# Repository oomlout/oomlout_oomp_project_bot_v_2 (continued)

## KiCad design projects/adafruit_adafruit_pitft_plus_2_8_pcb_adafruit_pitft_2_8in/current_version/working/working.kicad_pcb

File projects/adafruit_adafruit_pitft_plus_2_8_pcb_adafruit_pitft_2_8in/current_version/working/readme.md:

# adafruit_pitft_plus_2_8_pcb
 
## summary 
* id: adafruit_adafruit_pitft_plus_2_8_pcb_adafruit_pitft_2_8in
* user: adafruit
* name: adafruit_pitft_plus_2_8_pcb
* board: adafruit_pitft_2_8in
* repo: https://github.com/adafruit/Adafruit-PiTFT-Plus-2.8-PCB

* src_file_repo_sch: 
* src_file_repo_sch_link: https://github.com/adafruit/Adafruit-PiTFT-Plus-2.8-PCB/tree/master/
* full details link: https://github.com/oomlout/oomlout_oomp_project_bot_v_2/tree/main/projects/adafruit_adafruit_pitft_plus_2_8_pcb_adafruit_pitft_2_8in/current_version/working  

## schematic  
  
[schematic (pdf)](working_schematic.pdf) 

## pcb  

[board (pdf)](working.pdf)  

## working_bom
| Id | Designator | Footprint | Quantity | Designation | Supplier and ref |  | None | 
| --- | --- | --- | --- | --- | --- | --- | --- | 
| 1 | U$15,U$3,U$17,U$40,U$16 | MOUNTINGHOLE_3.0_PLATEDTHIN | 5 | MOUNTINGHOLE3.0THIN |  |  | [''] | 
| 2 | R1,R2,R4,R3 | 0805-NO | 4 | 100 |  |  | [''] | 
| 3 | R13,R12,R14,R9 | 0805-NO | 4 | 3.9K |  |  | [''] | 
| 4 | R18,R16,R15,R17 | 0805-NO | 4 | 0 |  |  | [''] | 
| 5 | D1,D2 | SOD-323 | 2 | 1N4148 |  |  | [''] | 
| 6 | R6,R7 | 0805-NO | 2 | 10K |  |  | [''] | 
| 7 | IC5 | SOT23 | 1 | APX803 |  |  | [''] | 
| 8 | U$12 | PCBFEAT-REV-040 | 1 |  |  |  | [''] | 
| 9 | U$18,U$10,U$11 | FIDUCIAL_1MM | 3 | FIDUCIAL" |  |  | [''] | 
| 10 | R11,R10 | 0805-NO | 2 | 22 |  |  | [''] | 
| 11 | JP3 | 2X20_SMT_MALE | 1 |  |  |  | [''] | 
| 12 | U2 | QFN16_3MM | 1 | STMPE811 |  |  | [''] | 
| 13 | WPJ1,WPJ0 | SOLDERJUMPER_CLOSEDWIRE | 2 |  |  |  | [''] | 
| 14 | C3,C4,C2 | 0805-NO | 3 | 0.1uF |  |  | [''] | 
| 15 | U1 | SOIC8_150MIL | 1 | CAT24C32 |  |  | [''] | 
| 16 | R8 | 0805-NO | 1 | DNP |  |  | [''] | 
| 17 | U$42 | ADAFRUIT_TEXT_30MM | 1 |  |  |  | [''] | 
| 18 | C1,C5 | 0805-NO | 2 | 10uF |  |  | [''] | 
| 19 | Q2 | SOT23-WIDE | 1 | BSS138 |  |  | [''] | 
| 20 | SW2,SW4,SW3,SW1 | TACT_PANA-EVQ | 4 |  |  |  | [''] | 
| 21 | U$23 | ADAFRUIT_TEXT_20MM | 1 |  |  |  | [''] | 
| 22 | U$2 | TFT_2.83IN_240X320_50PIN | 1 | DISP_LCD_240X320_50PIN_2.8IN |  |  | [''] | 
| 23 | RPI1 | RASPBERRYPI_BPLUS_SHIELD_NODIM | 1 | RASPBERRYPI_BPLUS_SHIELD_NODIM |  |  | [''] | 

## bom_schematic
| Ref | Qnty | Value | Cmp name | Footprint | Description | Vendor | DNP | 
| --- | --- | --- | --- | --- | --- | --- | --- | 
| C1, C5 | 2 | 10uF | CAP_CERAMIC0805-NOOUTLINE | working:0805-NO |  |  |  | 
| C2, C3, C4 | 3 | 0.1uF | CAP_CERAMIC0805-NOOUTLINE | working:0805-NO |  |  |  | 
| D1, D2 | 2 | 1N4148 | DIODESOD-323 | working:SOD-323 |  |  |  | 
| IC5 | 1 | APX803 | AXP083-SAG | working:SOT23 |  |  |  | 
| JP3 | 1 | PINHD-2X20_SMT | PINHD-2X20_SMT | working:2X20_SMT_MALE |  |  |  | 
| Q2 | 1 | BSS138 | MOSFET-NWIDE | working:SOT23-WIDE |  |  |  | 
| R1, R2, R3, R4 | 4 | 100 | RESISTOR0805_NOOUTLINE | working:0805-NO |  |  |  | 
| R6, R7 | 2 | 10K | RESISTOR0805_NOOUTLINE | working:0805-NO |  |  |  | 
| R8 | 1 | DNP | RESISTOR0805_NOOUTLINE | working:0805-NO |  |  |  | 
| R9, R12, R13, R14 | 4 | 3.9K | RESISTOR0805_NOOUTLINE | working:0805-NO |  |  |  | 
| R10, R11 | 2 | 22 | RESISTOR0805_NOOUTLINE | working:0805-NO |  |  |  | 
| R15, R16, R17, R18 | 4 | 0 | RESISTOR0805_NOOUTLINE | working:0805-NO |  |  |  | 
| RPI1 | 1 | RASPBERRYPI_BPLUS_SHIELD_NODIM | RASPBERRYPI_BPLUS_SHIELD_NODIM | working:RASPBERRYPI_BPLUS_SHIELD_NODIM |  |  |  | 
| SW1, SW2, SW3, SW4 | 4 | SWITCH_PUSHBUTTONEVQ-PE | SWITCH_PUSHBUTTONEVQ-PE | working:TACT_PANA-EVQ |  |  |  | 
| U1 | 1 | CAT24C32 | EEPROM_I2C_SOIC8_GENERIC | working:SOIC8_150MIL |  |  |  | 
| U2 | 1 | STMPE811 | STMPE610 | working:QFN16_3MM |  |  |  | 
| U$2 | 1 | DISP_LCD_240X320_50PIN_2.8IN | DISP_LCD_240X320_50PIN_2.8IN | working:TFT_2.83IN_240X320_50PIN |  |  |  | 
| U$3, U$15, U$16, U$17, U$40 | 5 | MOUNTINGHOLE3.0THIN | MOUNTINGHOLE3.0THIN | working:MOUNTINGHOLE_3.0_PLATEDTHIN |  |  |  | 
| U$10, U$11, U$18 | 3 | FIDUCIAL"" | FIDUCIAL{dblquote}{dblquote} | working:FIDUCIAL_1MM |  |  |  | 
| WPJ0, WPJ1 | 2 | SOLDERJUMPERCLOSED | SOLDERJUMPERCLOSED | working:SOLDERJUMPER_CLOSEDWIRE |  |  |  | 

## mounting_holes
| x | y | package | value | ref | size | 
| --- | --- | --- | --- | --- | --- | 
| 0.03 | 77.9 | MOUNTINGHOLE_3.0_PLATEDTHIN | MOUNTINGHOLE3.0THIN | U$3 | m3 | 
| 49.02 | 77.9 | MOUNTINGHOLE_3.0_PLATEDTHIN | MOUNTINGHOLE3.0THIN | U$15 | m3 | 
| 49.0 | 0.0 | MOUNTINGHOLE_3.0_PLATEDTHIN | MOUNTINGHOLE3.0THIN | U$16 | m3 | 
| 0.0 | 0.0 | MOUNTINGHOLE_3.0_PLATEDTHIN | MOUNTINGHOLE3.0THIN | U$17 | m3 | 
| 0.03 | 19.91 | MOUNTINGHOLE_3.0_PLATEDTHIN | MOUNTINGHOLE3.0THIN | U$40 | m3 |

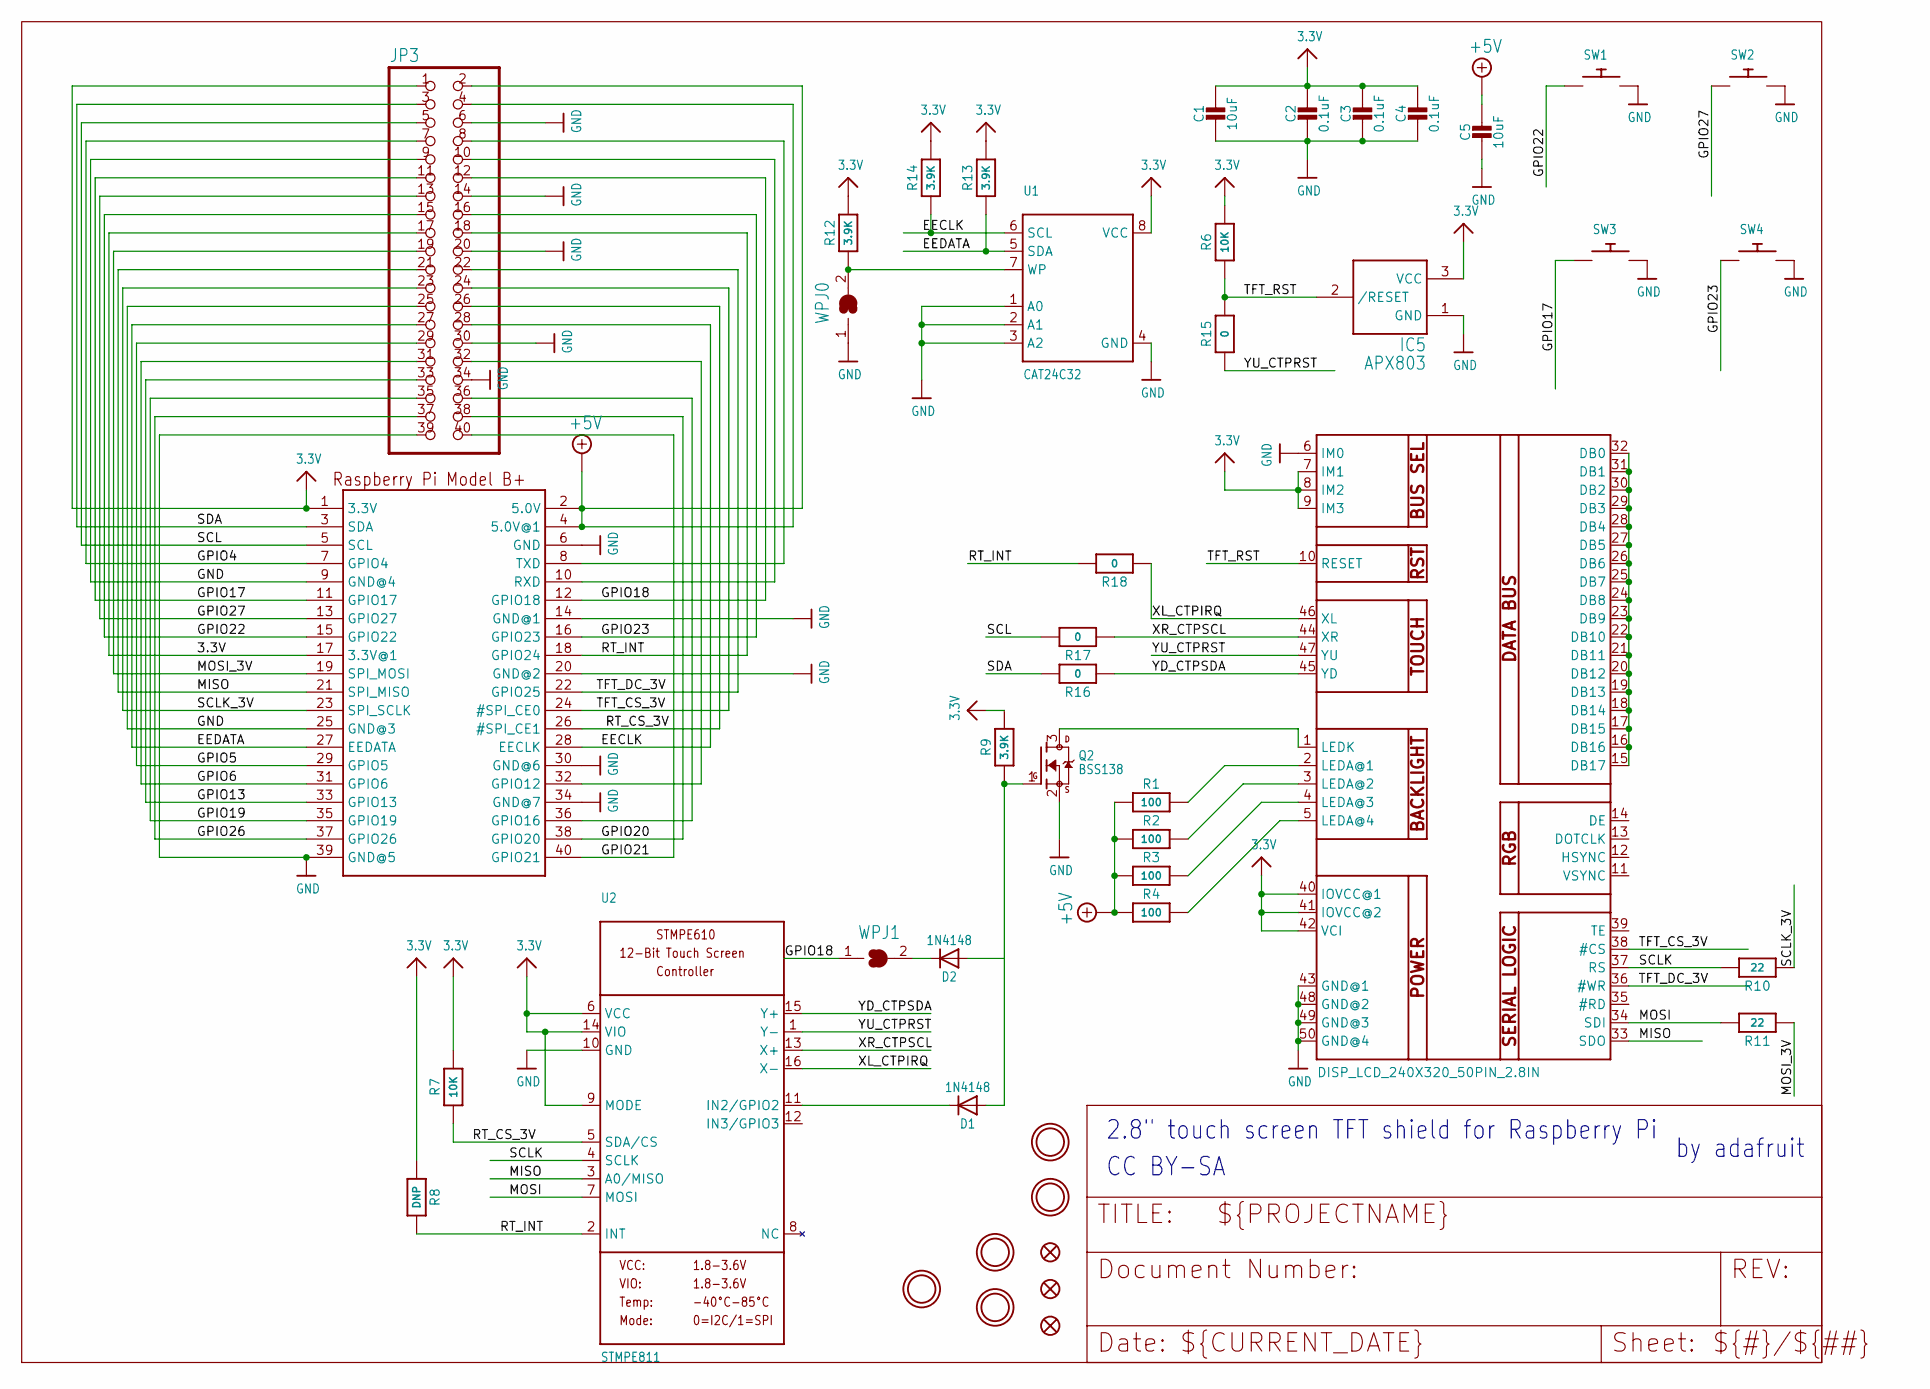
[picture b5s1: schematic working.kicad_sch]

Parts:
C1, C5: 10uF; 0805-NO
C2, C3, C4: 0.1uF; 0805-NO
D1, D2: 1N4148; SOD-323
IC5: APX803; SOT23
JP3: PINHD-2X20_SMT; 2X20_SMT_MALE
Q2: BSS138; SOT23-WIDE
R1, R2, R3, R4: 100; 0805-NO
R6, R7: 10K; 0805-NO
R8: DNP; 0805-NO
R9, R12, R13, R14: 3.9K; 0805-NO
R10, R11: 22; 0805-NO
R15, R16, R17, R18: 0; 0805-NO
RPI1: RASPBERRYPI_BPLUS_SHIELD_NODIM
SW1, SW2, SW3, SW4: SWITCH_PUSHBUTTONEVQ-PE; TACT_PANA-EVQ
U1: CAT24C32; SOIC8_150MIL
U2: STMPE811; QFN16_3MM
U$2: DISP_LCD_240X320_50PIN_2.8IN; TFT_2.83IN_240X320_50PIN
U$3, U$15, U$16, U$17, U$40: MOUNTINGHOLE3.0THIN; MOUNTINGHOLE_3.0_PLATEDTHIN
U$10, U$11, U$18: FIDUCIAL""; FIDUCIAL_1MM
WPJ0, WPJ1: SOLDERJUMPERCLOSED; SOLDERJUMPER_CLOSEDWIRE

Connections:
3.3V: C1.1, C2.1, C3.1, C4.1, IC5.3 (VCC), JP3.1, JP3.17, R6.2, R7.2, R8.1, R9.2, R12.2, R13.2, R14.2, RPI1.1 (3.3V), RPI1.17 (3.3V@1), U1.8 (VCC), U2.6 (VCC), U2.9 (MODE), U2.14 (VIO), U$2.7 (IM1), U$2.8 (IM2), U$2.9 (IM3), U$2.40 (IOVCC@1), U$2.41 (IOVCC@2), U$2.42 (VCI)
+5V: C5.1, JP3.2, JP3.4, R1.1, R2.1, R3.1, R4.1, RPI1.2 (5.0V), RPI1.4 (5.0V@1)
EECLK: JP3.28, R14.1, RPI1.28 (EECLK), U1.6 (SCL)
EEDATA: JP3.27, R13.1, RPI1.27 (EEDATA), U1.5 (SDA)
GND: C1.2, C2.2, C3.2, C4.2, C5.2, IC5.1 (GND), JP3.6, JP3.9, JP3.14, JP3.20, JP3.25, JP3.30, JP3.34, JP3.39, Q2.2 (S), RPI1.6 (GND), RPI1.9 (GND@4), RPI1.14 (GND@1), RPI1.20 (GND@2), RPI1.25 (GND@3), RPI1.30 (GND@6), RPI1.34 (GND@7), RPI1.39 (GND@5), SW1.P$2, SW2.P$2, SW3.P$2, SW4.P$2, U1.1 (A0), U1.2 (A1), U1.3 (A2), U1.4 (GND), U2.10 (GND), U$2.6 (IM0), U$2.43 (GND@1), U$2.48 (GND@2), U$2.49 (GND@3), U$2.50 (GND@4), WPJ0.1
GPIO4: JP3.7, RPI1.7 (GPIO4)
GPIO5: JP3.29, RPI1.29 (GPIO5)
GPIO6: JP3.31, RPI1.31 (GPIO6)
GPIO12: JP3.32, RPI1.32 (GPIO12)
GPIO13: JP3.33, RPI1.33 (GPIO13)
GPIO16: JP3.36, RPI1.36 (GPIO16)
GPIO17: JP3.11, RPI1.11 (GPIO17), SW3.P$1
GPIO18: JP3.12, RPI1.12 (GPIO18), WPJ1.1
GPIO19: JP3.35, RPI1.35 (GPIO19)
GPIO20: JP3.38, RPI1.38 (GPIO20)
GPIO21: JP3.40, RPI1.40 (GPIO21)
GPIO22: JP3.15, RPI1.15 (GPIO22), SW1.P$1
GPIO23: JP3.16, RPI1.16 (GPIO23), SW4.P$1
GPIO26: JP3.37, RPI1.37 (GPIO26)
GPIO27: JP3.13, RPI1.13 (GPIO27), SW2.P$1
MISO: JP3.21, RPI1.21 (SPI_MISO), U2.3 (A0/MISO), U$2.33 (SDO)
MOSI: R11.2, U2.7 (MOSI), U$2.34 (SDI)
MOSI_3V: JP3.19, R11.1, RPI1.19 (SPI_MOSI)
unnamed: Q2.3 (D), U$2.1 (LEDK)
unnamed: R1.2, U$2.2 (LEDA@1)
unnamed: R2.2, U$2.3 (LEDA@2)
unnamed: R3.2, U$2.4 (LEDA@3)
unnamed: D1.C, U2.11 (IN2/GPIO2)
unnamed: D2.C, WPJ1.2
unnamed: U$2.15 (DB17), U$2.16 (DB16), U$2.17 (DB15), U$2.18 (DB14), U$2.19 (DB13), U$2.20 (DB12), U$2.21 (DB11), U$2.22 (DB10), U$2.23 (DB9), U$2.24 (DB8), U$2.25 (DB7), U$2.26 (DB6), U$2.27 (DB5), U$2.28 (DB4), U$2.29 (DB3), U$2.30 (DB2), U$2.31 (DB1), U$2.32 (DB0)
unnamed: R4.2, U$2.5 (LEDA@4)
unnamed: R12.1, U1.7 (WP), WPJ0.2
RT_CS_3V: JP3.26, R7.1, RPI1.26 (#SPI_CE1), U2.5 (SDA/CS)
RT_INT: JP3.18, R8.2, R18.2, RPI1.18 (GPIO24), U2.2 (INT)
RXD: JP3.10, RPI1.10 (RXD)
SCL: JP3.5, R17.2, RPI1.5 (SCL)
SCLK: R10.2, U2.4 (SCLK), U$2.37 (RS)
SCLK_3V: JP3.23, R10.1, RPI1.23 (SPI_SCLK)
SDA: JP3.3, R16.2, RPI1.3 (SDA)
TFT_CS_3V: JP3.24, RPI1.24 (#SPI_CE0), U$2.38 (#CS)
TFT_DC_3V: JP3.22, RPI1.22 (GPIO25), U$2.36 (#WR)
TFT_RST: IC5.2 (/RESET), R6.1, R15.2, U$2.10 (RESET)
TXD: JP3.8, RPI1.8 (TXD)
XL_CTPIRQ: R18.1, U2.16 (X-), U$2.46 (XL)
XR_CTPSCL: R17.1, U2.13 (X+), U$2.44 (XR)
YD_CTPSDA: R16.1, U2.15 (Y+), U$2.45 (YD)
YU_CTPRST: R15.1, U2.1 (Y-), U$2.47 (YU)

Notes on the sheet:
by adafruit~{}
2.8" touch screen TFT shield for Raspberry Pi
CC BY-SA

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
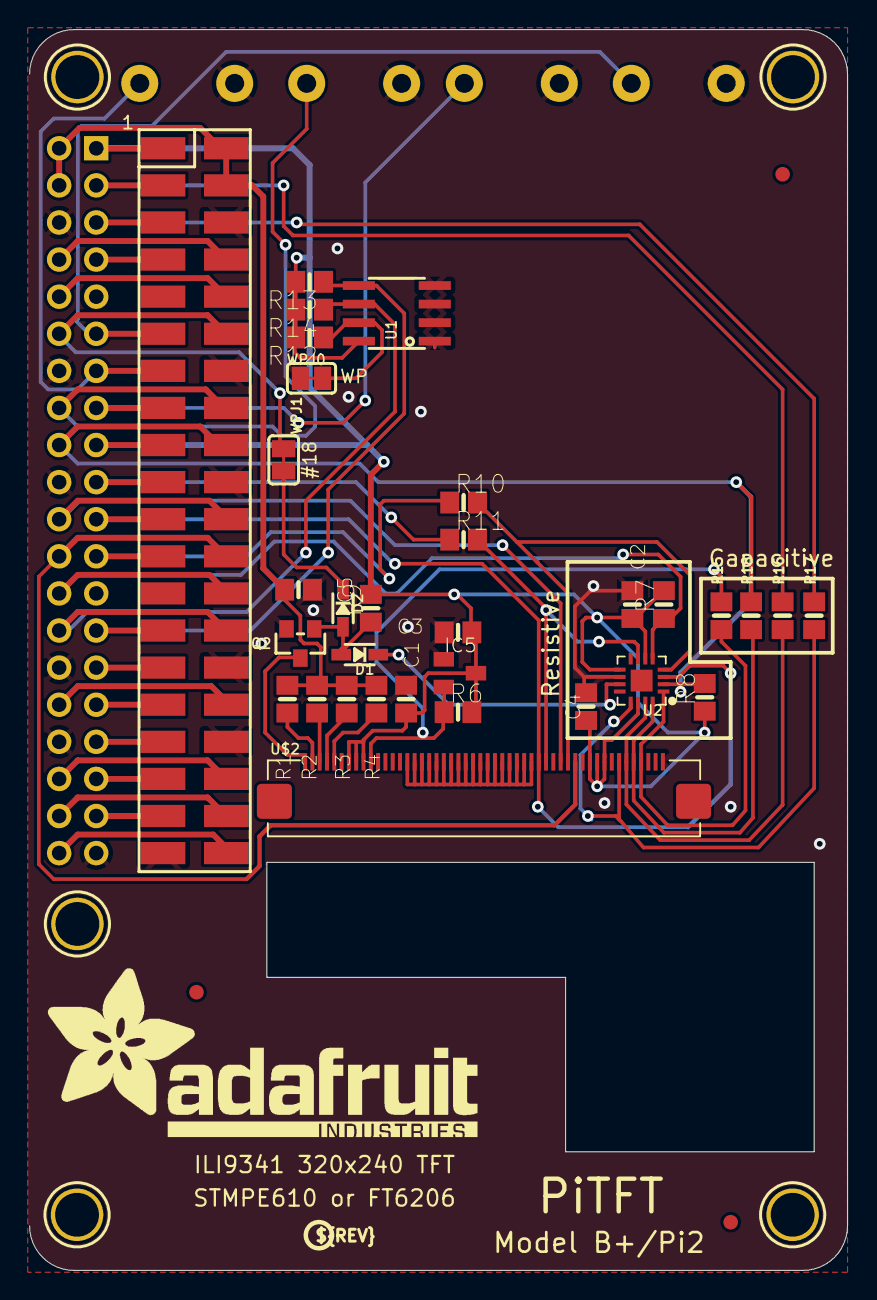
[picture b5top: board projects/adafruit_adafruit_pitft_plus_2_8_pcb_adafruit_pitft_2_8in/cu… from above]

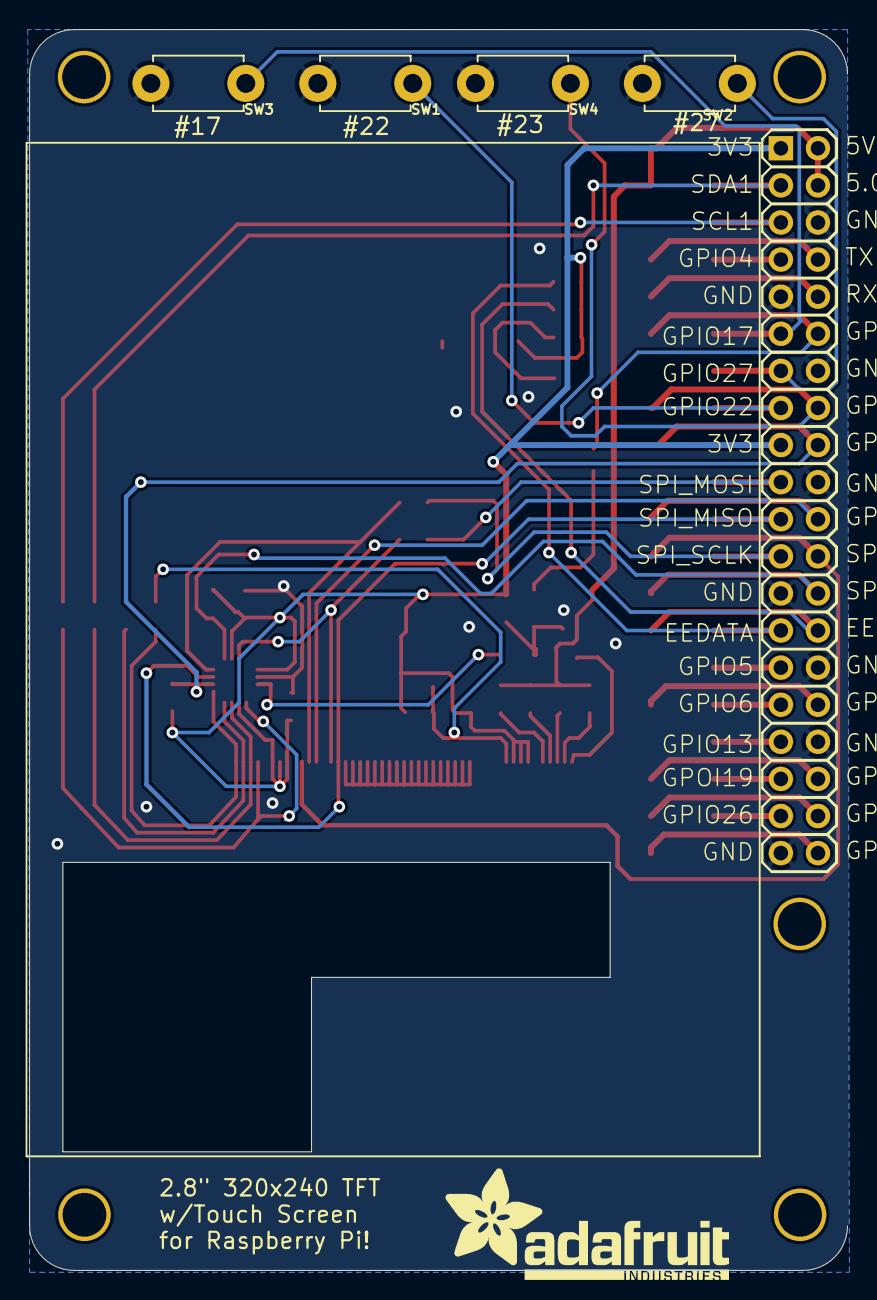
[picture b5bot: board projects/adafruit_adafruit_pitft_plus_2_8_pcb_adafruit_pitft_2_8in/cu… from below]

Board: 16 copper layers, 56.0 x 85.0 mm, 48 parts (7 on the bottom side), 48 nets.

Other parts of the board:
U$12: PCBFEAT-REV-040
U$23: ADAFRUIT_TEXT_20MM
U$42: ADAFRUIT_TEXT_30MM

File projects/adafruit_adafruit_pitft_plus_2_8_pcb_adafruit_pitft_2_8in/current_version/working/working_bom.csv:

"Id";"Designator";"Footprint";"Quantity";"Designation";"Supplier and ref";
1;"U$15,U$3,U$17,U$40,U$16";"MOUNTINGHOLE_3.0_PLATEDTHIN";5;"MOUNTINGHOLE3.0THIN";;;
2;"R1,R2,R4,R3";"0805-NO";4;"100";;;
3;"R13,R12,R14,R9";"0805-NO";4;"3.9K";;;
4;"R18,R16,R15,R17";"0805-NO";4;"0";;;
5;"D1,D2";"SOD-323";2;"1N4148";;;
6;"R6,R7";"0805-NO";2;"10K";;;
7;"IC5";"SOT23";1;"APX803";;;
8;"U$12";"PCBFEAT-REV-040";1;"";;;
9;"U$18,U$10,U$11";"FIDUCIAL_1MM";3;"FIDUCIAL""";;;
10;"R11,R10";"0805-NO";2;"22";;;
11;"JP3";"2X20_SMT_MALE";1;"";;;
12;"U2";"QFN16_3MM";1;"STMPE811";;;
13;"WPJ1,WPJ0";"SOLDERJUMPER_CLOSEDWIRE";2;"";;;
14;"C3,C4,C2";"0805-NO";3;"0.1uF";;;
15;"U1";"SOIC8_150MIL";1;"CAT24C32";;;
16;"R8";"0805-NO";1;"DNP";;;
17;"U$42";"ADAFRUIT_TEXT_30MM";1;"";;;
18;"C1,C5";"0805-NO";2;"10uF";;;
19;"Q2";"SOT23-WIDE";1;"BSS138";;;
20;"SW2,SW4,SW3,SW1";"TACT_PANA-EVQ";4;"";;;
21;"U$23";"ADAFRUIT_TEXT_20MM";1;"";;;
22;"U$2";"TFT_2.83IN_240X320_50PIN";1;"DISP_LCD_240X320_50PIN_2.8IN";;;
23;"RPI1";"RASPBERRYPI_BPLUS_SHIELD_NODIM";1;"RASPBERRYPI_BPLUS_SHIELD_NODIM";;;

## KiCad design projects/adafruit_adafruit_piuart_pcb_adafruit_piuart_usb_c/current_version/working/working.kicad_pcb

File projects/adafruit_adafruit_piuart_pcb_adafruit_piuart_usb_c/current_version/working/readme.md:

# adafruit_piuart_pcb
 
## summary 
* id: adafruit_adafruit_piuart_pcb_adafruit_piuart_usb_c
* user: adafruit
* name: adafruit_piuart_pcb
* board: adafruit_piuart_usb_c
* repo: https://github.com/adafruit/Adafruit-PiUART-PCB

* src_file_repo_sch: 
* src_file_repo_sch_link: https://github.com/adafruit/Adafruit-PiUART-PCB/tree/master/
* full details link: https://github.com/oomlout/oomlout_oomp_project_bot_v_2/tree/main/projects/adafruit_adafruit_piuart_pcb_adafruit_piuart_usb_c/current_version/working  

## schematic  
  
[schematic (pdf)](working_schematic.pdf) 

## pcb  

[board (pdf)](working.pdf)  

## working_bom
| Id | Designator | Footprint | Quantity | Designation | Supplier and ref |  | None | 
| --- | --- | --- | --- | --- | --- | --- | --- | 
| 1 | ON/OFF0 | EG1390 | 1 | EG1390 |  |  | [''] | 
| 2 | U$9 | RASPBERRYPI_2X5_THMSMT | 1 | RASPBERRYPI_2X5 |  |  | [''] | 
| 3 | R5,R2 | 0603-NO | 2 | 47K |  |  | [''] | 
| 4 | R6 | 0603-NO | 1 | 20K |  |  | [''] | 
| 5 | X2 | USB_C_CUSB31-CFM2AX-01-X | 1 |  |  |  | [''] | 
| 6 | U$18 | MOUNTINGHOLE_3.0_PLATEDTHIN | 1 | MOUNTINGHOLE3.0THIN |  |  | [''] | 
| 7 | T2 | SOT-23 | 1 | DMG3415U |  |  | [''] | 
| 8 | FID2,FID1,FID4,FID3 | FIDUCIAL_1MM | 4 | FIDUCIAL_1MM |  |  | [''] | 
| 9 | C1,C2,C3 | 0805-NO | 3 | 10uF |  |  | [''] | 
| 10 | C4 | 0603-NO | 1 | 0.1uF |  |  | [''] | 
| 11 | D1 | CHIPLED_0603_NOOUTLINE | 1 | RED |  |  | [''] | 
| 12 | R1 | RESPACK_4X0603 | 1 | 5.1K |  |  | [''] | 
| 13 | D3 | CHIPLED_0603_NOOUTLINE | 1 | GREEN |  |  | [''] | 
| 14 | D2 | CHIPLED_0603_NOOUTLINE | 1 | YELLOW |  |  | [''] | 
| 15 | U$8 | ADAFRUIT_2.5MM | 1 |  |  |  | [''] | 
| 16 | R3 | 0603-NO | 1 | 5.1K |  |  | [''] | 
| 17 | U1 | QFN24_4MM_SMSC | 1 | CP2104 |  |  | [''] | 
| 18 | U$17 | PCBFEAT-REV-040 | 1 |  |  |  | [''] | 
| 19 | SJ1 | SOLDERJUMPER_CLOSEDWIRE | 1 |  |  |  | [''] | 

## bom_schematic
| Ref | Qnty | Value | Cmp name | Footprint | Description | Vendor | DNP | 
| --- | --- | --- | --- | --- | --- | --- | --- | 
| C1, C2, C3 | 3 | 10uF | CAP_CERAMIC0805-NOOUTLINE | working:0805-NO |  |  |  | 
| C4 | 1 | 0.1uF | CAP_CERAMIC0603_NO | working:0603-NO |  |  |  | 
| D1 | 1 | RED | LED0603_NOOUTLINE | working:CHIPLED_0603_NOOUTLINE |  |  |  | 
| D2 | 1 | YELLOW | LED0603_NOOUTLINE | working:CHIPLED_0603_NOOUTLINE |  |  |  | 
| D3 | 1 | GREEN | LED0603_NOOUTLINE | working:CHIPLED_0603_NOOUTLINE |  |  |  | 
| FID1, FID2, FID3, FID4 | 4 | FIDUCIAL_1MM | FIDUCIAL_1MM | working:FIDUCIAL_1MM |  |  |  | 
| ON/OFF0 | 1 | EG1390 | DPDT-EG1390 | working:EG1390 |  |  |  | 
| R1 | 1 | 5.1K | RESISTOR_4PACK | working:RESPACK_4X0603 |  |  |  | 
| R2, R5 | 2 | 47K | RESISTOR_0603_NOOUT | working:0603-NO |  |  |  | 
| R3 | 1 | 5.1K | RESISTOR_0603_NOOUT | working:0603-NO |  |  |  | 
| R6 | 1 | 20K | RESISTOR_0603_NOOUT | working:0603-NO |  |  |  | 
| SJ1 | 1 | SOLDERJUMPERCLOSED | SOLDERJUMPERCLOSED | working:SOLDERJUMPER_CLOSEDWIRE |  |  |  | 
| T2 | 1 | DMG3415U | PMOSSOT23 | working:SOT-23 |  |  |  | 
| U1 | 1 | CP2104 | CP2104 | working:QFN24_4MM_SMSC |  |  |  | 
| U$9 | 1 | RASPBERRYPI_2X5 | RASPBERRYPI_2X5 | working:RASPBERRYPI_2X5_THMSMT |  |  |  | 
| U$18 | 1 | MOUNTINGHOLE3.0THIN | MOUNTINGHOLE3.0THIN | working:MOUNTINGHOLE_3.0_PLATEDTHIN |  |  |  | 
| X2 | 1 | USB_C | USB_C | working:USB_C_CUSB31-CFM2AX-01-X |  |  |  | 

## mounting_holes
| x | y | package | value | ref | size | 
| --- | --- | --- | --- | --- | --- | 
| 0.0 | 0.0 | MOUNTINGHOLE_3.0_PLATEDTHIN | MOUNTINGHOLE3.0THIN | U$18 | m3 |

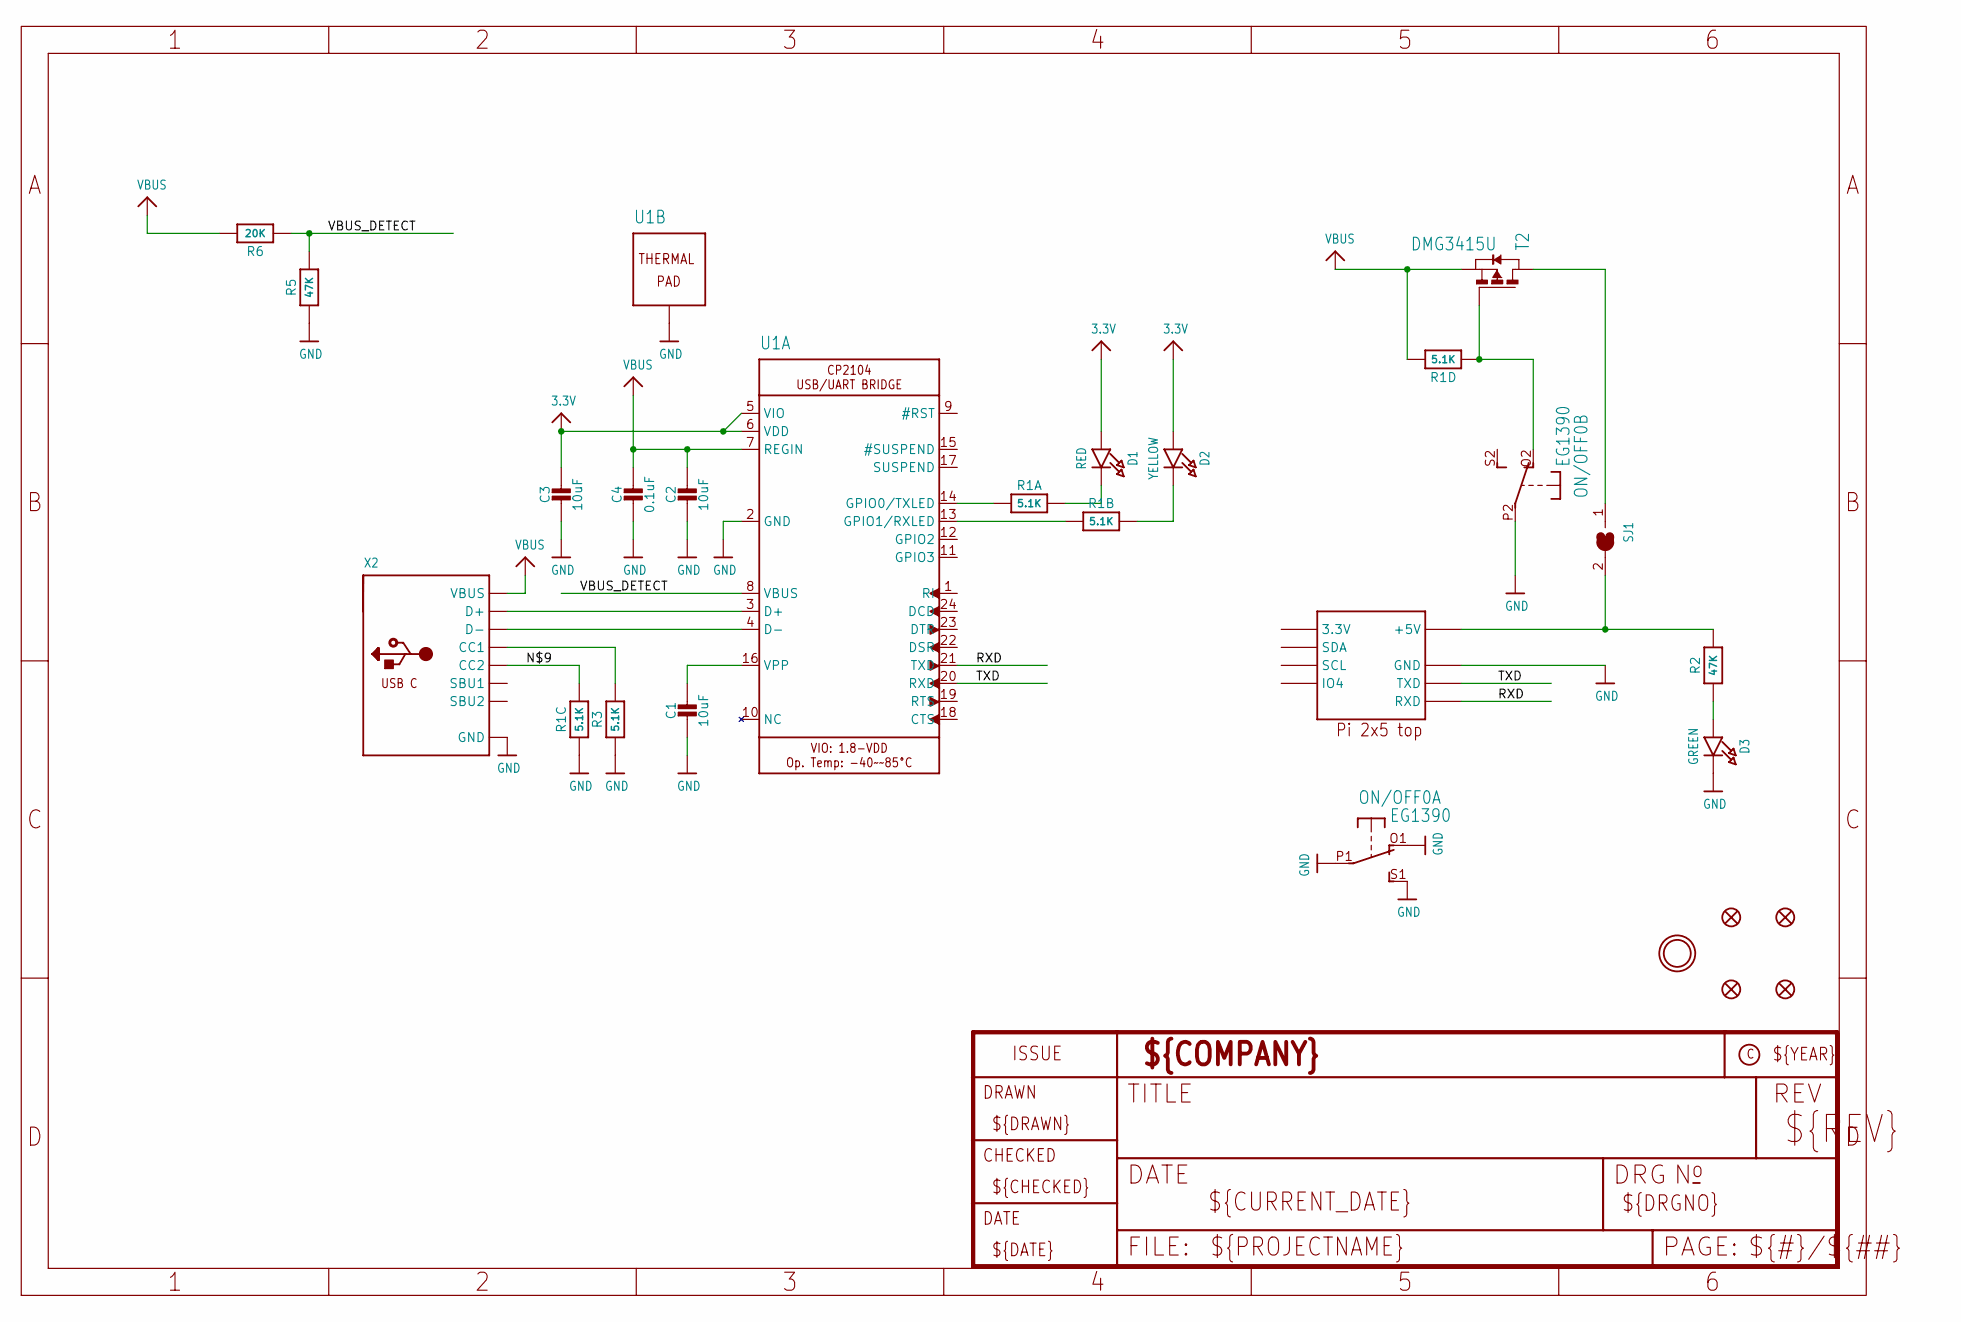
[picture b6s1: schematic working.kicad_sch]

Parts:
C1, C2, C3: 10uF; 0805-NO
C4: 0.1uF; 0603-NO
D1: RED; CHIPLED_0603_NOOUTLINE
D2: YELLOW; CHIPLED_0603_NOOUTLINE
D3: GREEN; CHIPLED_0603_NOOUTLINE
FID1, FID2, FID3, FID4: FIDUCIAL_1MM
ON/OFF0: EG1390
R1: 5.1K; RESPACK_4X0603
R2, R5: 47K; 0603-NO
R3: 5.1K; 0603-NO
R6: 20K; 0603-NO
SJ1: SOLDERJUMPERCLOSED; SOLDERJUMPER_CLOSEDWIRE
T2: DMG3415U; SOT-23
U1: CP2104; QFN24_4MM_SMSC
U$9: RASPBERRYPI_2X5; RASPBERRYPI_2X5_THMSMT
U$18: MOUNTINGHOLE3.0THIN; MOUNTINGHOLE_3.0_PLATEDTHIN
X2: USB_C; USB_C_CUSB31-CFM2AX-01-X

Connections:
3.3V: C3.1, D1.A, D2.A, U1.5 (VIO), U1.6 (VDD)
5V: R2.2, SJ1.2, U$9.2 (+5V), U$9.2' (+5V), U$9.4 (+5V), U$9.4' (+5V)
GND: C1.2, C2.2, C3.2, C4.2, D3.C, ON/OFF0.O1 (O), ON/OFF0.P1, ON/OFF0.P2, ON/OFF0.S1 (S), R1.3 (1), R3.1, R5.1, U1.2 (GND), U1.THERM (TP), U$9.6 (GND), U$9.6' (GND), U$9.9 (GND), U$9.9' (GND), X2.A1B12 (GND), X2.B1A12 (GND)
unnamed: D3.A, R2.1
unnamed: U1.3 (D+), X2.A6 (D+), X2.B6 (D+)
unnamed: U1.4 (D-), X2.A7 (D-), X2.B7 (D-)
unnamed: C1.1, U1.16 (VPP)
unnamed: R1.1, U1.14 (GPIO0/TXLED)
unnamed: D1.C, R1.8 (2)
unnamed: R1.2 (1), U1.13 (GPIO1/RXLED)
unnamed: D2.C, R1.7 (2)
unnamed: R1.6 (2), X2.B5 (CC2)
unnamed: R3.2, X2.A5 (CC1)
unnamed: ON/OFF0.O2 (O), R1.4 (1), T2.3 (G)
NC1: U$9.1 (3.3V), U$9.1' (3.3V)
NC2: U$9.3 (SDA), U$9.3' (SDA)
NC3: U$9.5 (IO4), U$9.5' (IO4)
NC4: U$9.7 (SCL), U$9.7' (SCL)
RXD: U1.21 (TXD), U$9.10 (RXD), U$9.10' (RXD)
TXD: U1.20 (RXD), U$9.8 (TXD), U$9.8' (TXD)
VBUS: C2.1, C4.1, R1.5 (2), R6.2, T2.2 (S), U1.7 (REGIN), X2.A4B9 (VBUS), X2.B4A9 (VBUS)
VBUS_DETECT: R5.2, R6.1, U1.8 (VBUS)
VIN: SJ1.1, T2.1 (D)

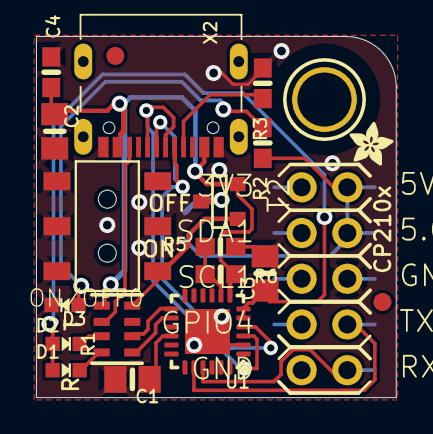
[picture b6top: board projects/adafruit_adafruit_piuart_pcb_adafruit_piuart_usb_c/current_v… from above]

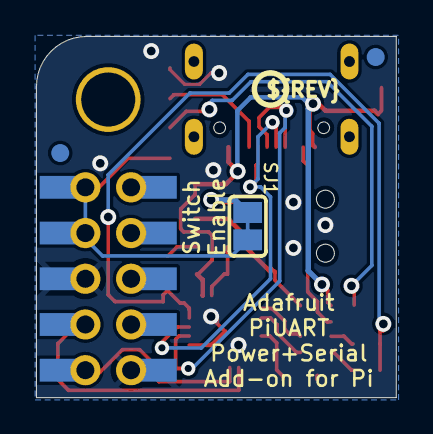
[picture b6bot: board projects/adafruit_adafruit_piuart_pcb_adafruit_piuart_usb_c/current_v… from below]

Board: 2 copper layers, 20.0 x 20.1 mm, 25 parts (4 on the bottom side), 23 nets.

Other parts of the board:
U$8: ADAFRUIT_2.5MM
U$17: PCBFEAT-REV-040

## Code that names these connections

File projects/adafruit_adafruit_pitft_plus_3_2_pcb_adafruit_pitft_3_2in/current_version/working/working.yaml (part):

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  null:
  - ''
- Id: '6'
  Designator: GPIO5,GPIO12,GPIO26,GPIO6,GPIO13,GPIO20,GPIO19,GPIO21,GPIO16
  Footprint: PAD-1.5X2.0
  Quantity: '9'
  Designation: ''
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  \ |  | 28 |  |  |  | [''] | \n| 2 | C4 | 0805-NO | 1 | 0.1uF |  |  | [''] | \n|\
  \ 3 | R15,R2,R17,R16,R1,R18 | 0805-NO | 6 | 100 |  |  | [''] | \n| 4 | D4,D3 | SOD-323\
  \ | 2 | 1N4148 |  |  | [''] | \n| 5 | R12,R13,R14,R20 | 0805-NO | 4 | 3.9K |  |\
  \  | [''] | \n| 6 | GPIO5,GPIO12,GPIO26,GPIO6,GPIO13,GPIO20,GPIO19,GPIO21,GPIO16\
  \ | PAD-1.5X2.0 | 9 |  |  |  | [''] | \n| 7 | Q2 | SOT23-WIDE | 1 | BSS138 |  |\
  \  | [''] | \n| 8 | R6,R11,R7 | 0805-NO | 3 | 10K |  |  | [''] | \n| 9 | R23 | _0805MP\
  \ | 1 | 22 |  |  | [''] | \n| 10 | WPJ1 | SOLDERJUMPER_CLOSEDWIRE | 1 |  |  |  |\
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  Description: ''
  Footprint: working:PAD-1.5X2.0
  Qnty: '9'
  Ref: GPIO5, GPIO6, GPIO12, GPIO13, GPIO16, GPIO19, GPIO20, GPIO21, GPIO26
  Value: TESTPOINT1.5X2.0MM_NOCREAM
  Vendor: ''
- Cmp name: AXP083-SAG
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  \ | Vendor | DNP | \n| --- | --- | --- | --- | --- | --- | --- | --- | \n| C1 |\
  \ 1 | 10uF | CAP_CERAMIC0805-NOOUTLINE | working:0805-NO |  |  |  | \n| C4 | 1 |\
  \ 0.1uF | CAP_CERAMIC0805-NOOUTLINE | working:0805-NO |  |  |  | \n| D3, D4 | 2\
  \ | 1N4148 | DIODESOD-323 | working:SOD-323 |  |  |  | \n| GPIO5, GPIO6, GPIO12,\
  \ GPIO13, GPIO16, GPIO19, GPIO20, GPIO21, GPIO26 | 9 | TESTPOINT1.5X2.0MM_NOCREAM\
  \ | TESTPOINT1.5X2.0MM_NOCREAM | working:PAD-1.5X2.0 |  |  |  | \n| IC5 | 1 | AXP803\
  \ | AXP083-SAG | working:SOT23 |  |  |  | \n| JP1 | 1 | HEADER-2X13-SMT | HEADER-2X13-SMT\
  \ | working:2X13_SMT_MALE |  |  |  | \n| Q2 | 1 | BSS138 | MOSFET-NWIDE | working:SOT23-WIDE\
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  Rot: 180.0
  Side: top
  Val: 1N4148
- '# Ref': GPIO5
  Package: PAD-1.5X2.0
  PosX: 126.5936
  PosY: -132.9436
  Rot: 90.0
  Side: top
  Val: .nan
- '# Ref': GPIO6
  Package: PAD-1.5X2.0
  PosX: 126.5936
  PosY: -130.4036
  Rot: 90.0
  Side: top
  Val: .nan
- '# Ref': GPIO12
  Package: PAD-1.5X2.0
  PosX: 122.2756
  PosY: -130.4036
  Rot: 90.0
  Side: top
  Val: .nan
- '# Ref': GPIO13
  Package: PAD-1.5X2.0
  PosX: 126.5936
  PosY: -127.8636
  Rot: 90.0
  Side: top
  Val: .nan
- '# Ref': GPIO16
  Package: PAD-1.5X2.0
  PosX: 122.2756
  PosY: -127.8636
  Rot: 90.0
  Side: top
  Val: .nan
- '# Ref': GPIO19
  Package: PAD-1.5X2.0
  PosX: 126.5936
  PosY: -125.3236
  Rot: 90.0
  Side: top
  Val: .nan
- '# Ref': GPIO20
  Package: PAD-1.5X2.0
  PosX: 122.2756
  PosY: -125.3236
  Rot: 90.0
  Side: top
  Val: .nan
- '# Ref': GPIO21
  Package: PAD-1.5X2.0
  PosX: 122.2756
  PosY: -122.7836
  Rot: 90.0
  Side: top
  Val: .nan
- '# Ref': GPIO26
  Package: PAD-1.5X2.0
  PosX: 126.5936
  PosY: -122.7836
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  \ | -147.4216 | 0.0 | top | \n| C1 | 10uF | 0805-NO | 170.4086 | -104.8766 | 0.0\
  \ | top | \n| C4 | 0.1uF | 0805-NO | 161.8996 | -100.6856 | 90.0 | top | \n| D3\
  \ | 1N4148 | SOD-323 | 135.6106 | -104.2416 | 180.0 | top | \n| D4 | 1N4148 | SOD-323\
  \ | 135.6106 | -102.3366 | 180.0 | top | \n| GPIO5 | nan | PAD-1.5X2.0 | 126.5936\
  \ | -132.9436 | 90.0 | top | \n| GPIO6 | nan | PAD-1.5X2.0 | 126.5936 | -130.4036\
  \ | 90.0 | top | \n| GPIO12 | nan | PAD-1.5X2.0 | 122.2756 | -130.4036 | 90.0 |\
  \ top | \n| GPIO13 | nan | PAD-1.5X2.0 | 126.5936 | -127.8636 | 90.0 | top | \n\
  | GPIO16 | nan | PAD-1.5X2.0 | 122.2756 | -127.8636 | 90.0 | top | \n| GPIO19 |\
  \ nan | PAD-1.5X2.0 | 126.5936 | -125.3236 | 90.0 | top | \n| GPIO20 | nan | PAD-1.5X2.0\
  \ | 122.2756 | -125.3236 | 90.0 | top | \n| GPIO21 | nan | PAD-1.5X2.0 | 122.2756\
  \ | -122.7836 | 90.0 | top | \n| GPIO26 | nan | PAD-1.5X2.0 | 126.5936 | -122.7836\
  \ | 90.0 | top | \n| IC5 | AXP803 | SOT23 | 169.6466 | -110.4646 | 0.0 | top | \n\
  | JP1 | nan | 2X13_SMT_MALE | 149.1996 | -72.8726 | 0.0 | top | \n| Q2 | BSS138\
  \ | SOT23-WIDE | 133.3246 | -107.2896 | 180.0 | top | \n| R1 | 100 | 0805-NO | 134.8486\
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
